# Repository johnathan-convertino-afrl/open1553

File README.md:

# open1553

Respository of open source 1553 designs for the pmod1553 device.

author: Jay Convertino   
   
date: 2021.07.29  
   
details: FPGA devices used via a PMOD mil-std-1553 electrical interface device to decode and encode 1553 transmissions.  
   
license: Various   
   
Special thanks to Analog Devices, their HDL build system is fantastic. I've used it with modifications in the HDL directory.  

## RELEASE VERSIONS
### Current
  - release_1553_v2 (releases are tags)
    * added analog switch for proper 1553 multiplexing
    * added en_diff for switch toggling
  
### Past
  - release_1553_v1 (releases are tags)
    * first public release

## Requirements
### HDL
  - Vivado 2018.3.1
  - Icarus
  
### Software
  - GCC
  - DTC
  
## Quick Start
0. fifo_pmod1553/fmc1553 projects require linux. See docs folder for creating SDCARD.
1. Install Vivado 2018.3.1
2. Install build essentials package for Ubuntu.
3. From the root of the HDL directory you may run the following build commands.
    - make uart_pmod1553.arty-a7-35
    - make uart_pmod1553.cmod-s7-25
    - make fifo_pmod1553.zedboard
    - make fifo_pmod1553.zcu102
    - make fifo_pmod1553.zybo (OLD ZYBO NOT Z7)
    - make fmc1553.zcu102
4. Once completed you may use Vivado to open the project (xpr will be in the project folder root). To program your development board via JTAG.
    - You will need to add a memory configuration device to write the bitstream to the flash of the cmod/arty.
    - cmod example at: https://reference.digilentinc.com/learn/programmable-logic/tutorials/cmod-a7-programming-guide/start?_ga=2.262285964.1885041324.1628539712-1298016575.1609856716
    - Again, for the fifo/fmc projects you oned to build the linux system. See the docs folder for instructions.
  
## USAGE
### General Usage

For xilinx fifo and uart the format is the same.   
Data is received in the following ASCII string format:  
>CMDS;D1;P1;I0;Hx5555\r  
>DATA;D0;P1;I0;HxAAAA\r  

The fields are seperated by ; .   
  
  - The first is the sync type, Command/Status = CMDS, Data = DATA
  - The second is if there is a 4us delay, 1 = delay over 4us, 0 = no delay or less then 4us.
  - The third is parity, 1 = parity good, 0 = parity bad
  - The fourth is invert, 1 = core is inverting data, 0 = core is not inverting data
  - The fifth is the data in hex format, Hx???? where ? = 4 bits of data (16 bits in total).
  - The carrige return is the string terminator. This works well with serial consoles with local newline addition enabled.
      - tr '\r' '\n' is your friend for xilinx fifo applications.
      
Data is sent in the following ASCII string format:  
>CMDS;D1;P1;I0;Hx5555\r  
>DATA;D0;P1;I0;HxAAAA\r  

The fields are seperated by ; .   
  
  - The first is the sync type, Command/Status = CMDS, Data = DATA
  - The second is to enable a 4us delay, 1 = delay of at least 4us, 0 = no delay or less then 4us.
  - The third is parity, 1 = parity odd (default), 0 = parity even
  - The fourth is invert, 1 = invert data, 0 = don't invert data
  - The fifth is the data in hex format, Hx???? where ? = 4 bits of data (16 bits in total).
  - The carrige return is the string terminator.
      - echo -ne "DATA;D1;P1;I0;Hx5555\r" is your friend for xilinx fifo applications.

## DIRECTORIES
### docs

Helpful documents for the open1553 systems.

The subfolder diagrams contains high level block diagrams of the 1553 data flow.

The subfolder linux_build contrains documents for Linux on the Zedboard, ZCU102,   
and other targets.

### apps

Example applications for using the uart/fifo1553 in with python. Won't set the world   
on fire performance wise, but shows how quickly something can be put together.

Python2 seems to be the best for fifo1553, python3 seems to be the best for the uart1553.  

### hardware

Hardware design and information for the pmod_1553 device.   
This design is drafted in KiCAD version 5.x.   

Open the KiCAD project file in hardware/pmod/kicad. This will allow you to  
look over the schematic and board design. You may then export it to whatever format   
needed for your PCB manufacturing process.  

### HDL

FPGA files for pmod_1553 projects. It contains libraries that are the  
actual code for IP cores, and projects that generate for target boards.  
Currently Supported:   

  - Digilent Arty 35T (UART DEVICE)
  - Digilent CMOD S7  (UART DEVICE)
  - Digilent Nexys A7 100t (UART DEVICE)
  - Zedboard (Xilinx FIFO pmod1553)
  - Zybo ORIGINAL (Xilinx FIFO pmod1553)
  - ZCU102 (Xilinx FIFO fmc1553)
  - ZCU102 (Xilinx FIFO pmod1553)

The original source for the HDL build system is from Analog Devices, all copyrights   
are there own and I claim no ownership of their code.

The original code has been altered and simulation capibility added.

HDL code built with Vivado 2018.3.1

The HDL build systems requires both Vivado and Icarus if you run a make all.   
If you make individual projects or cores you or may not need icarus. Vivado is a  
hard requirement.

Example:
>make uart_pmod1553.arty-a7-35

Will only run vivado to generate the target.   

See IP core (library folder) for details on simulation and usage.

### linux

Linux is for Xilinx AXIS FIFO projects, or any future Linux based designes.

axisfifo is a repository that contains the linux kernel driver source code for the   
Xilinx Axis FIFO ip. This has been included in the linux_kernel dev_fmc1553 branch   

zed/zcu102 is a folder of files to generate the boot binary. You may use the bootgen_files   
to create a new BOOT.bin. BOOT.bin is a complete build for the 2019_R1 release that can be  
used on the zedboard as is with the Analog Devices SDCARD image. The device three is also  
included in the same folder.    

The reference base image file is included for SDCARD imaging. (2019_R1-2020_06_22.img.xz)

## FUTURE
Todo list for v3
  - Consider adding high speed opamps to receive and transmit paths.
  - Add AXI core with custom linux driver for MIL-STD-1553 core.
    - Option between string and binary output.
    - Add ability to manipulate clock waveform... for fun. (v3.X)
  - High Speed C program to act as bus controller/remote terminal (v3.X)

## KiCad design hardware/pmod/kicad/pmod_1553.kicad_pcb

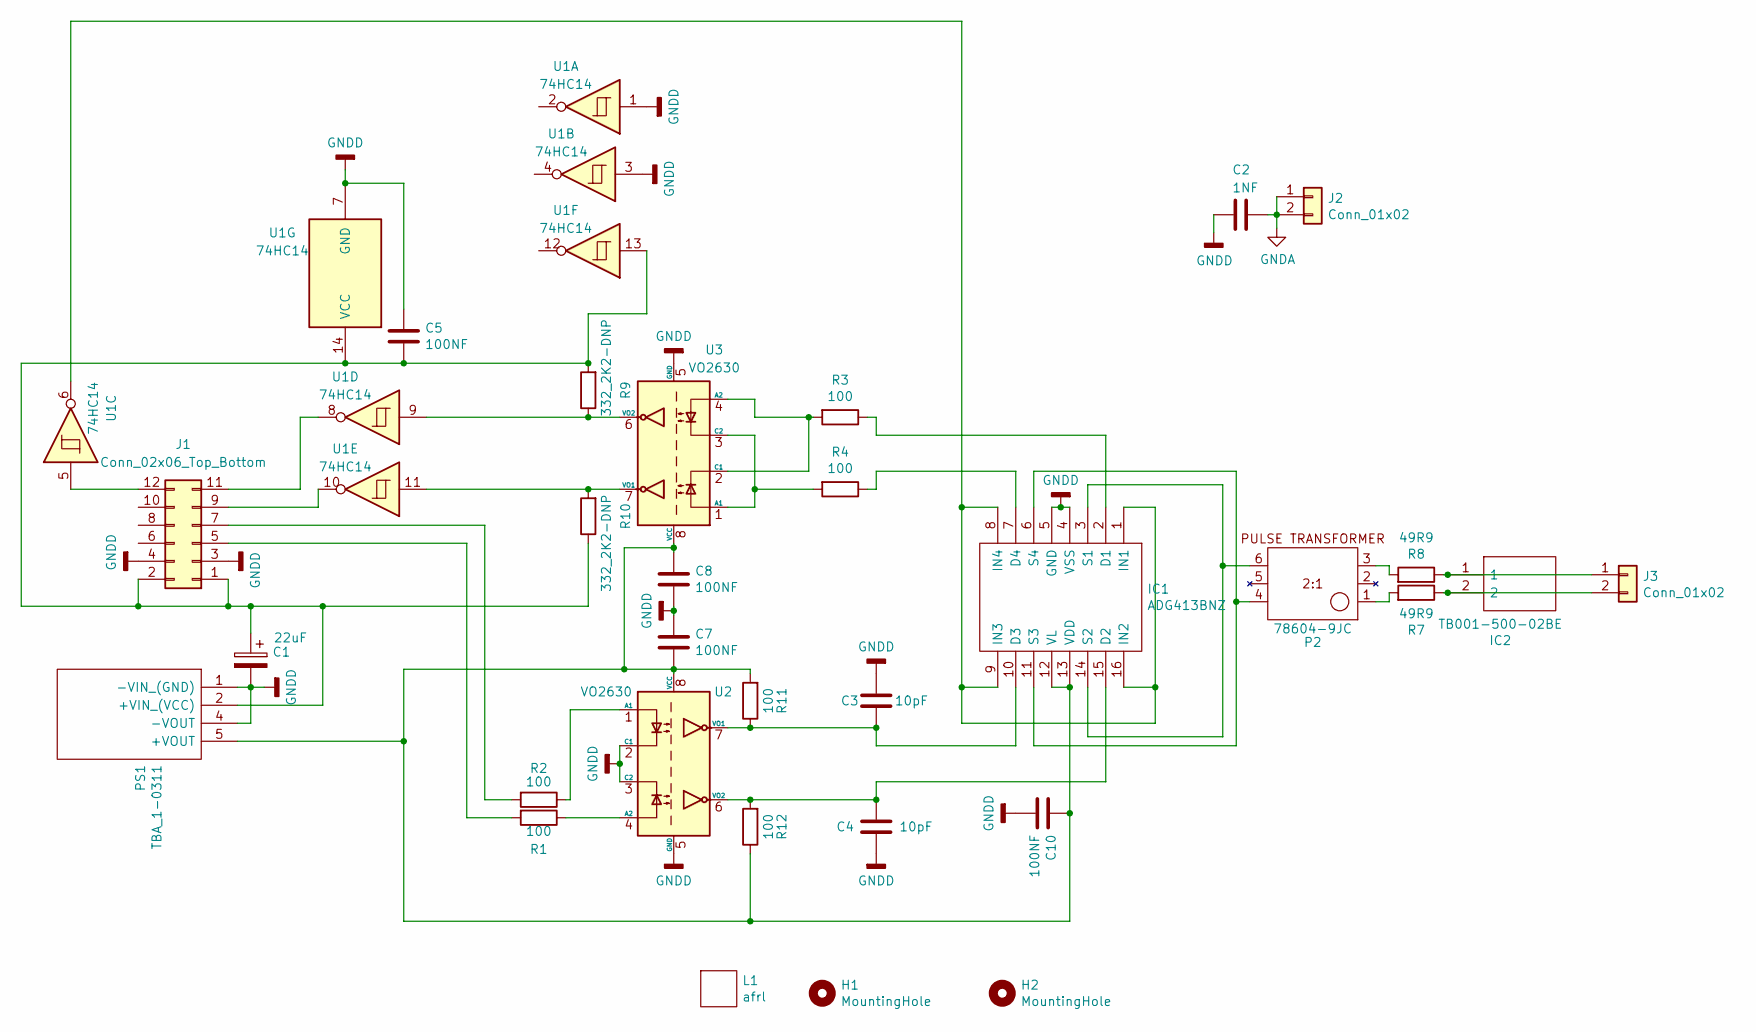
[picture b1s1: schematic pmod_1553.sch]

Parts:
C1: 22uF; CP_Radial_D5.0mm_P2.50mm
C2: 1NF; C_Disc_D4.7mm_W2.5mm_P5.00mm
C3, C4: 10pF; C_Disc_D4.7mm_W2.5mm_P5.00mm
C5, C7, C8, C10: 100NF; C_Disc_D4.7mm_W2.5mm_P5.00mm
H1, H2: MountingHole; MountingHole_2.2mm_M2_DIN965
IC1: ADG413BNZ; DIP-16_W7.62mm_LongPads; Manufacturer_Part_Number ADG413BNZ
IC2: TB001-500-02BE; TB00150002BE; Manufacturer_Part_Number TB001-500-02BE; Mouser Part Number 490-TB001-500-02BE
J1: Conn_02x06_Top_Bottom; PinHeader_2x06_P2.54mm_Horizontal
J2: Conn_01x02; Molex_KK-254_AE-6410-02A_1x02_P2.54mm_Vertical
J3: Conn_01x02; PinHeader_1x02_P2.54mm_Vertical
L1: afrl
P2: 78604-9JC
PS1: TBA_1-0311; TBA10311; Manufacturer_Part_Number TBA 1-0311; Mouser Part Number 495-TBA1-0311
R1, R2, R3, R4, R11, R12: 100; R_Axial_DIN0207_L6.3mm_D2.5mm_P7.62mm_Horizontal
R7, R8: 49R9; R_Axial_DIN0207_L6.3mm_D2.5mm_P7.62mm_Horizontal
R9, R10: 332_2K2-DNP; R_Axial_DIN0207_L6.3mm_D2.5mm_P7.62mm_Horizontal
U1: 74HC14; DIP-14_W7.62mm_LongPads
U2, U3: VO2630; DIP-8_W7.62mm

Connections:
GNDA: C2.1, J2.1, J2.2
GNDD: C1.2, C2.2, C3.1, C4.2, C5.1, C7.1, C8.2, C10.2, IC1.4 (VSS), IC1.5 (GND), J1.3, J1.4, PS1.1 (-VIN_(GND)), PS1.4 (-VOUT), U1.1, U1.3, U1.7 (GND), U2.2 (C1), U2.3 (C2), U2.5 (GND), U3.5 (GND)
unnamed: C1.1, C5.2, J1.1, J1.2, PS1.2 (+VIN_(VCC)), R9.2, R10.1, U1.13, U1.14 (VCC)
unnamed: C3.2, IC1.10 (D3), R11.1, U2.7 (VO1)
unnamed: C4.1, IC1.15 (D2), R12.2, U2.6 (VO2)
unnamed: C7.2, C8.1, C10.1, IC1.12 (VL), IC1.13 (VDD), PS1.5 (+VOUT), R11.2, R12.1, U2.8 (VCC), U3.8 (VCC)
unnamed: IC1.1 (IN1), IC1.8 (IN4), IC1.9 (IN3), IC1.16 (IN2), U1.6
unnamed: IC1.2 (D1), R3.1
unnamed: IC1.7 (D4), R4.1
unnamed: IC1.6 (S4), IC1.11 (S3), P2.4
unnamed: IC1.3 (S1), IC1.14 (S2), P2.6
unnamed: IC2.1, J3.1, R8.1
unnamed: IC2.2, J3.2, R7.1
unnamed: J1.5, R1.2
unnamed: J1.7, R2.2
unnamed: J1.9, U1.10
unnamed: J1.11, U1.8
unnamed: J1.12, U1.5
unnamed: P2.1, R7.2
unnamed: P2.3, R8.2
unnamed: R1.1, U2.4 (A2)
unnamed: R2.1, U2.1 (A1)
unnamed: R3.2, U3.2 (C1), U3.4 (A2)
unnamed: R4.2, U3.1 (A1), U3.3 (C2)
unnamed: R9.1, U1.9, U3.6 (VO2)
unnamed: R10.2, U1.11, U3.7 (VO1)

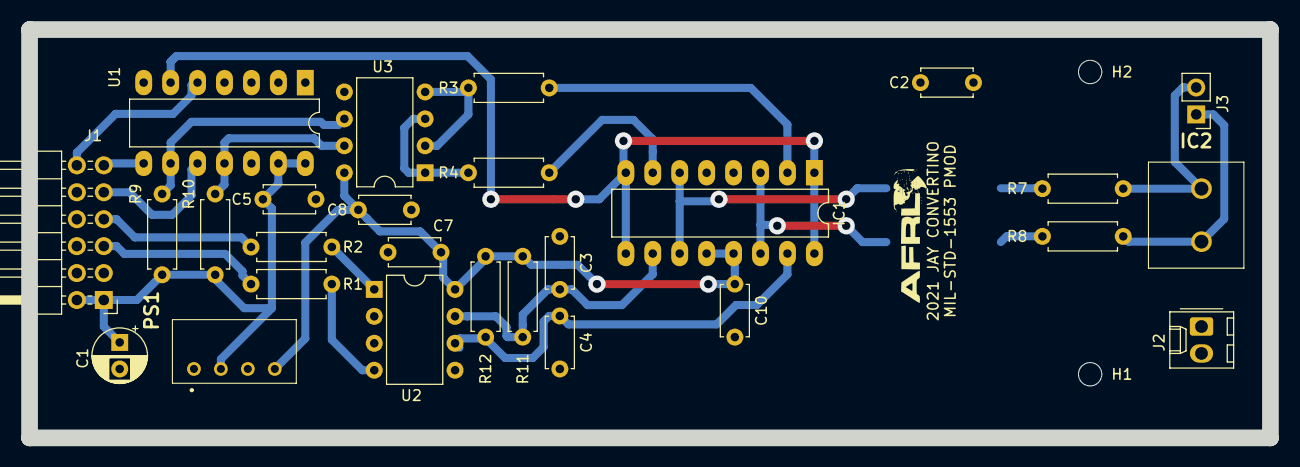
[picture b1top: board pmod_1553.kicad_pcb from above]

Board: 2 copper layers, 117.0 x 38.5 mm, 31 parts (1 on the bottom side), 26 nets.

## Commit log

2021-07-29 initial commit, needs better documentation and util_fifo/axis_xfifo test bench converted to verilog
2021-08-01 updated schematic with output filter caps on recieve line. Added AFRL logo as a library so it won't get deleted.
2021-08-02 added testbench for fifos,they are barebones junk, but they are there and work with icarus.
2021-08-02 updated gerber files with design fixes. Readme got a few additions.
2021-08-02 added alion fmc1553 board to project. tested build and intergration.
2021-08-05 added 1553 to fmc1553 core, need adc/dac interface connection. added arty mcs file.
2021-08-05 updated diff cores with correct names and quick testbench
2021-08-05 various fixes for timing errors and correcting clocks for fmc1553
2021-08-09 added fmc1553 kernel mods and fixes for axis fifo build and device tree generation for fifo pmod1553
2021-08-09 added documents for linux build, dac switch added, and pcb has small updates.
2021-08-09 added a few words about mcs file gen
2021-08-11 updated fmc1553 for encoder, it operates as it should. Buffer, DDS, and 1553 work. Buffer has priority if any data is sent to it.
2021-08-11 fix tcl script to remove unwanted port grouping
2021-08-11 cleanup readme
2021-08-12 added zcu102 to pmod1553 project. Updated documents to reflect this change and added device tree to kernel.
2021-08-13 organized documents folder, added flow documents subfolder
2021-08-13 remove hidden file
2021-08-13 added clock domains
2021-08-19 updated linux submodule
2021-08-19 example python apps, nothing special just somehthing to show the interface
2021-08-19 added apps info to readme
2021-08-19 made handshaking a bit more robust
2021-08-23 added debugs to help fix uart issues. Currently rx sync is off. Latest changes help, though it doesn't seem to be 100% fixed
2021-08-24 updates to uart to fix some more data issues. Added pipelines for RX/TX data that can be set to any length. Added pipelines to baud_gen cores to adjust uart_ena output as well. This allows for the da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
2021-08-24 updated util_uart_1553 with new rx/tx delay parameters
2021-08-24 updated projects with new specs for clock and uart core
2021-08-24 removed debug
2021-08-24 fixed reset routing for clock
2021-08-24 readded basic python examples for uart/fifo usage. These are NOT optimized and are terrible code, but do the job for a demo
2021-08-24 updated readme for uart
2021-08-24 schematic cleanup, add pdf for easy viewing on git
2021-08-24 fixed 3D library paths
2021-08-24 updated readme and pmod pic
2021-08-25 added bill of materials
2021-08-26 kicad url updates, they break removing the ? and after, but its clearer in seeing the make/model
2021-08-26 bom updates
2021-08-31 added zybo documents and updated data
2021-08-31 added zybo to pmod1553
2021-08-31 added quick start for uart strings
2021-08-31 added u-boot repo
2021-08-31 remove old files, everything is in place to generate new ones
2021-08-31 removed redundant file and updated readme with thankyoucomeagain
2021-08-31 updated readme formatting
2021-10-04 update readme with v2 information
2021-10-04 changed to lfs
2021-11-29 added adg413 switch to pmod1553, added symbols and data sheets for the adg413 and mcp6d11.
2021-12-13 updated encoder with diff enable line. Added said line to needed cores and projects. Build untested.
2021-12-13 updated readme version info
2021-12-22 updated diagrams for half duplex, pmod v2
2021-12-28 fixed a bug in the reset gen for cmod s7, reset high for cmod, not low (copy pasta error from A7 design).
2021-12-28 added first version of C code to simulate a bus controller transfering a file to a remote terminal. This is not tested, besides it compiles (this will not work).
2021-12-29 first version that works, far from perfect. Need to optimize and remove string functions from RT. Need to work on serial vs fifo read write (was thinking fifo, testing with serial causes issues)
2021-12-29 non-working apps, complete rewrite creating threads in a seperate lib for mil-std-1553
2021-12-29 first version that compiles, applications need the threads setup. Makefiles updated, but still meh.
2022-01-05 removed c example, wasn't very good. Will revisit for version 3. This commit also contains various small fixes.
2022-01-05 last commit for version 2, updated readme
2022-01-05 fixed readme, it was a mess
2022-01-05 one more try
2022-04-03 added nexus to master, not complete
2022-04-18 changed uart to loop cts/rts (does nothing in the core... yet). Added nexys uart project. Build tested, not hardware approved
2022-04-19 fixed uart lines and changed the names so they make sense now
2022-08-17 fixed gitignore, and fixed cleanup for 2020.2.2 since it creates a gen folder
2024-08-07 Delete linux/2019_R1-2020_06_22.img.xz
    Please download from analog devices website.
